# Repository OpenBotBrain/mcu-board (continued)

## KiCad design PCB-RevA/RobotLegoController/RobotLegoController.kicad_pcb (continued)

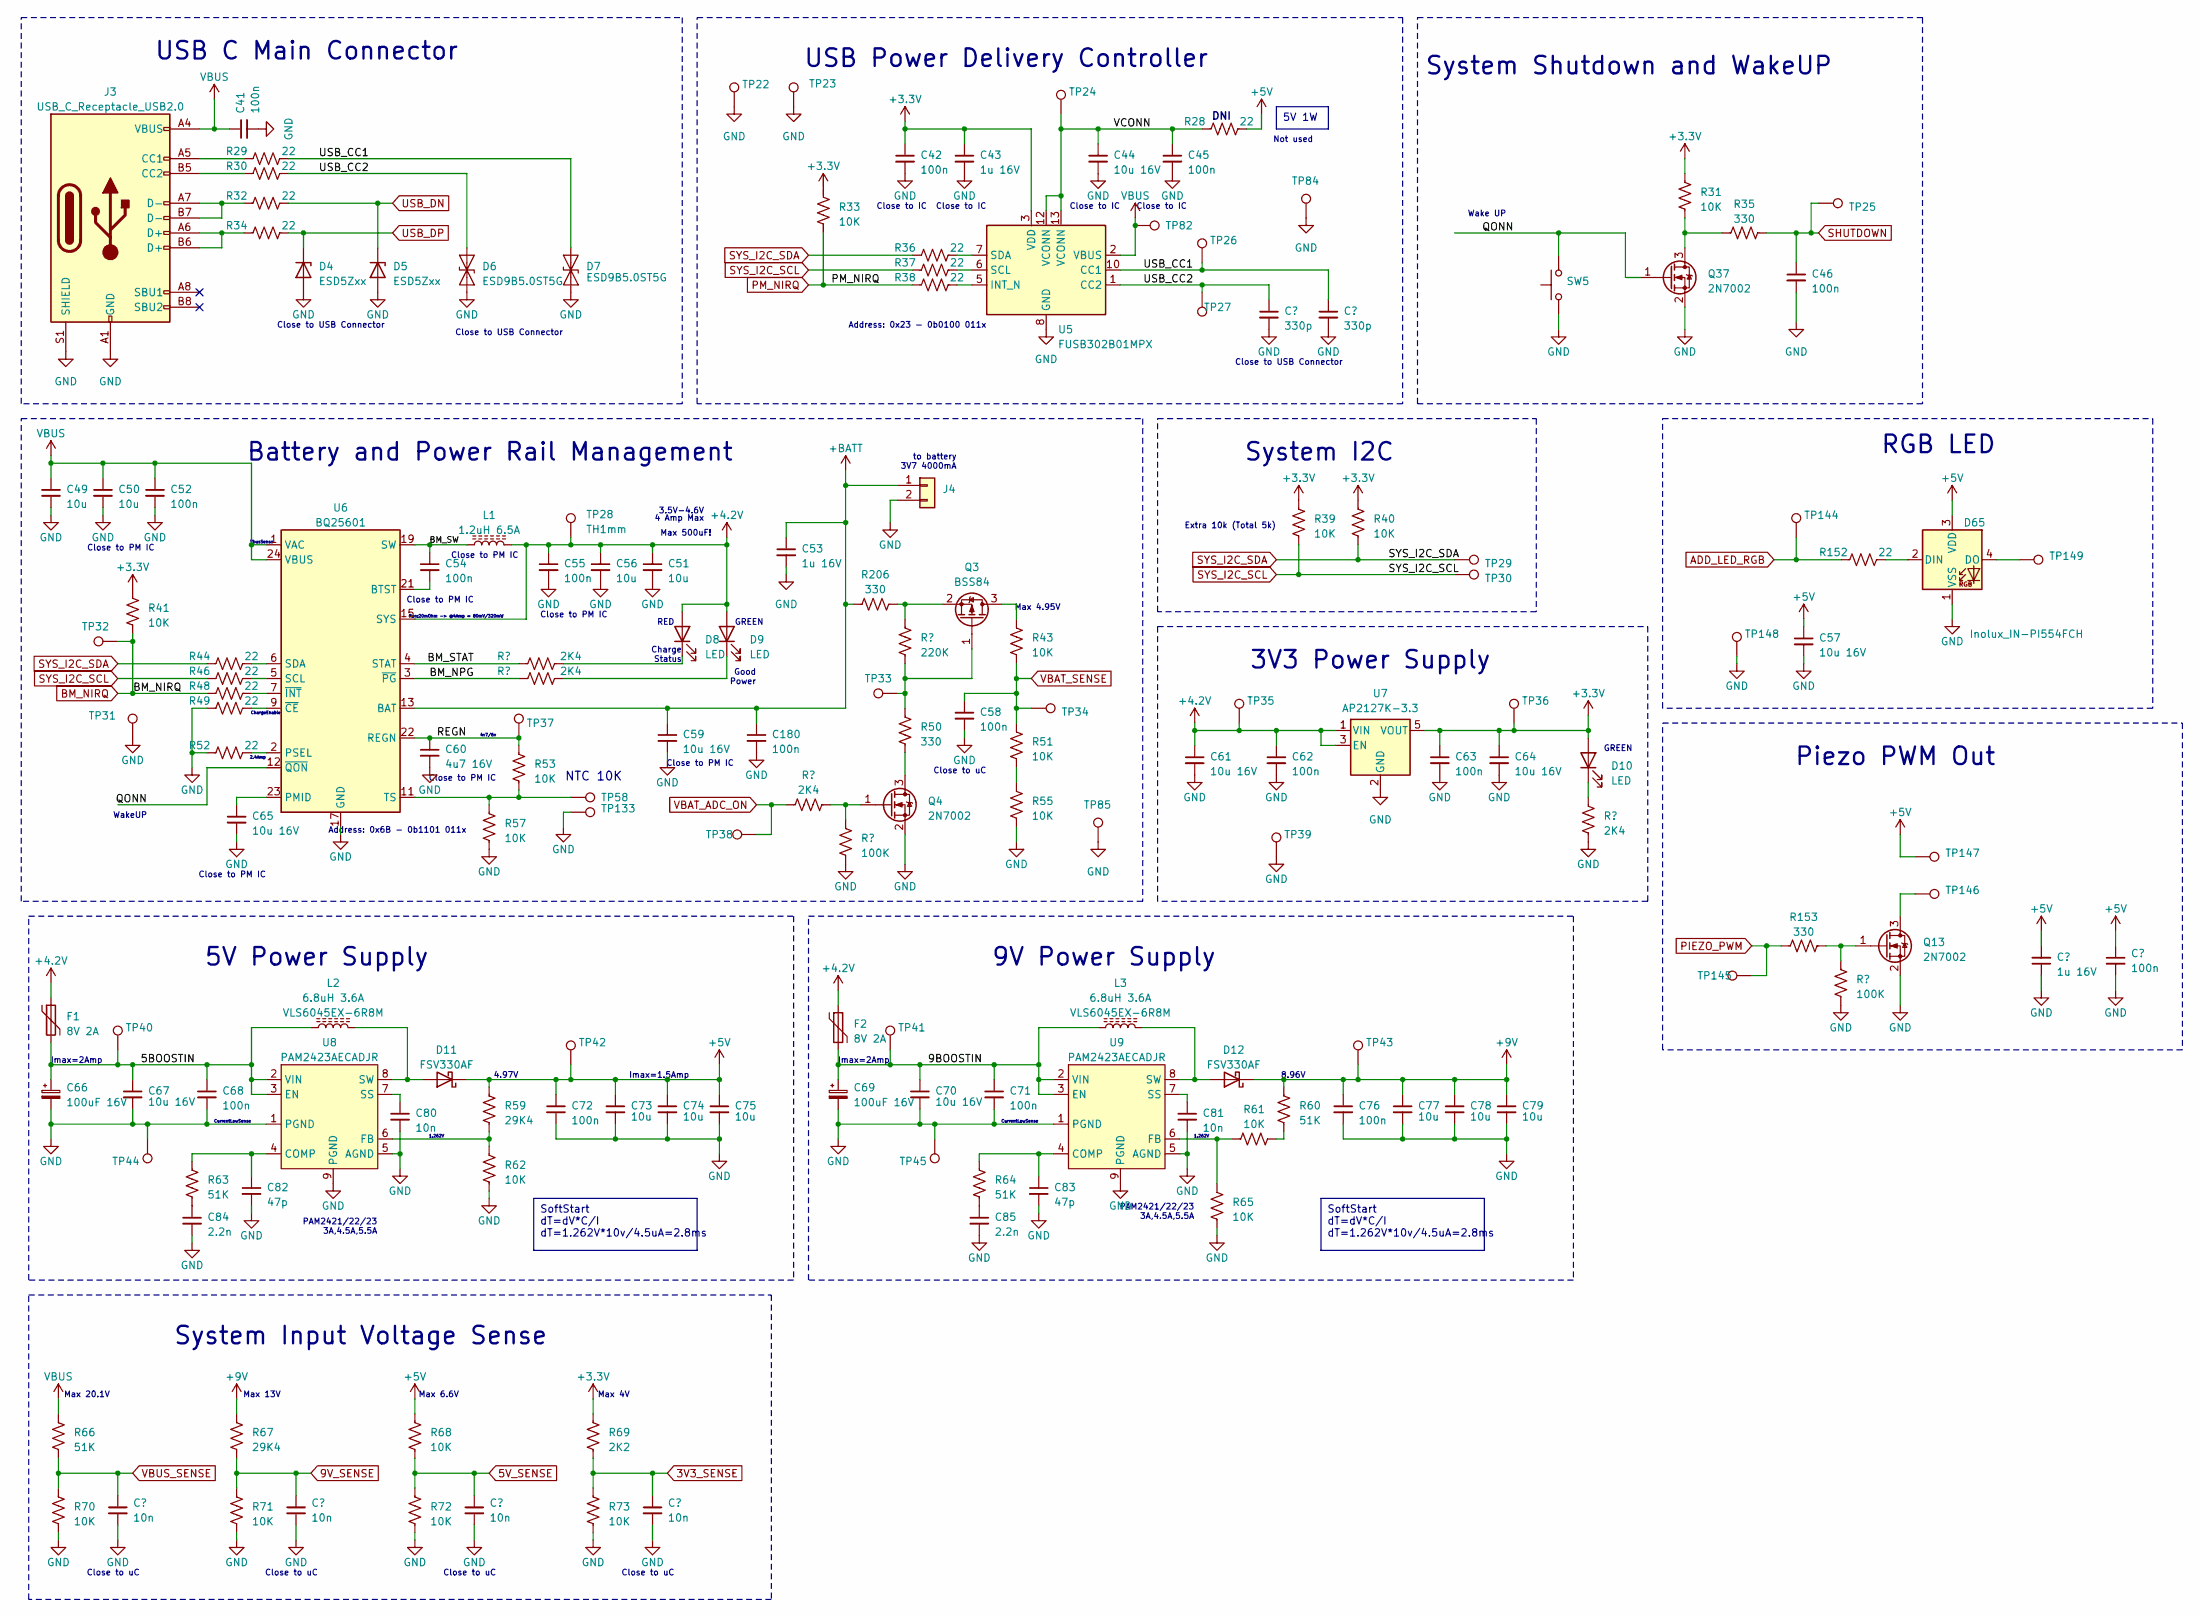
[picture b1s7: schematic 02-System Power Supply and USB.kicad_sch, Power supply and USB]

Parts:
C41, C42, C45, C46, C52, C54, C55, C58, C62, C63, C68, C71, C72, C76, C93, C180: 100n; C_0402_1005Metric
C43, C53, C92: 1u 16V; C_0603_1608Metric
C44, C57, C59, C61, C64, C65, C67, C70: 10u 16V; C_0805_2012Metric
C47, C48: 330p; C_0402_1005Metric
C49, C50, C51, C56, C73, C74, C75, C77, C78, C79: 10u; C_0805_2012Metric
C60: 4u7 16V; C_0603_1608Metric
C66, C69: 100uF 16V; CP_Elec_6.3x5.2
C80, C81, C86, C87, C88, C89: 10n; C_0402_1005Metric
C82, C83: 47p; C_0402_1005Metric
C84, C85: 2.2n; C_0402_1005Metric
D4, D5: ESD5Zxx; D_SOD-523
D6, D7: ESD9B5.0ST5G; D_SOD-923
D8, D9, D10: LED; LED_0402_1005Metric
D11, D12: FSV330AF; D_SOD-128
D65: Inolux_IN-PI554FCH; LED_Inolux_IN-PI554FCH_PLCC4_5.0x5.0mm_P3.2mm
F1, F2: 8V 2A; R_1812_4532Metric
J3: USB_C_Receptacle_USB2.0; USB_C_Receptacle_Palconn_UTC16-G
J4: Conn_01x02; JST_PH_B2B-PH-K_1x02_P2.00mm_Vertical
L1: 1.2uH 6.5A; L_Chilisin_BMRA00050520
L2, L3: 6.8uH 3.6A; L_Ferrocore_DLG-0504
Q3: BSS84; SOT-23
Q4, Q13, Q37: 2N7002; SOT-23
R28, R29, R30, R32, R34, R36, R37, R38, R44, R46, R48, R49, R52, R152: 22; R_0402_1005Metric
R31, R33, R39, R40, R41, R43, R51, R53, R55, R57, R61, R62, R65, R68, R70, R71, R72, R73: 10K; R_0402_1005Metric
R35, R50, R153, R206: 330; R_0402_1005Metric
R45, R47, R54, R56: 2K4; R_0402_1005Metric
R58, R154: 100K; R_0402_1005Metric
R59, R67: 29K4; R_0402_1005Metric
R60, R63, R64, R66: 51K; R_0402_1005Metric
R69: 2K2; R_0402_1005Metric
R168: 220K; R_0402_1005Metric
SW5: SW_Omron_B3FS; SW_Push_1P1T_NO_6x6mm_H9.5mm
TP22, TP24, TP25, TP26, TP27, TP29, TP30, TP31, TP32, TP33, TP34, TP35, TP36, TP37, TP38, TP39, TP40, TP41, TP42, TP43, TP44, TP45, TP58, TP82, TP84, TP85, TP144, TP145, TP148: S1mm; TestPoint_Pad_1.0x1.0mm
TP23, TP28, TP133, TP146, TP147, TP149: TH1mm; TestPoint_THTPad_1.0x1.0mm_Drill0.5mm
U5: FUSB302B01MPX; WQFN-14-1EP_2.5x2.5mm_P0.5mm_EP1.45x1.45mm
U6: BQ25601; Texas_S-PWQFN-N24_EP2.7x2.7mm_ThermalVias
U7: AP2127K-3.3; SOT-23-5
U8, U9: PAM2423AECADJR; SOIC-8-1EP_3.9x4.9mm_P1.27mm_EP2.29x3mm_ThermalVias

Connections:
3V3_SENSE: C89.1, R69.1, R73.2; also elsewhere on the board
5V_SENSE: C88.1, R68.1, R72.2; also elsewhere on the board
9V_SENSE: C87.1, R67.1, R71.2; also elsewhere on the board
+3.3V: C42.1, C43.1, C63.1, C64.1, D10.2 (A), R31.2, R33.2, R39.2, R40.2, R41.2, R69.2, TP36.1, U5.3 (VDD), U5.4 (VDD), U7.5 (VOUT); also elsewhere on the board
+4V: C51.1, C55.1, C56.1, C61.1, C62.1, D8.2 (A), D9.2 (A), F1.1, F2.1, L1.2, TP28.1, TP35.1, U6.15 (SYS), U6.16 (SYS), U7.1 (VIN), U7.3 (EN)
+9V: C76.1, C77.1, C78.1, C79.1, D12.1 (K), R60.2, R67.2, TP43.1; also elsewhere on the board
+BATT: C53.1, C59.1, C180.1, J4.1, R206.1, U6.13 (BAT), U6.14 (BAT)
/02-System Power Supply and USB/5BOOSTIN: C66.1, C67.1, C68.1, F1.2, L2.1, TP40.1, U8.2 (VIN), U8.3 (EN)
/02-System Power Supply and USB/9BOOSTIN: C69.1, C70.1, C71.1, F2.2, L3.1, TP41.1, U9.2 (VIN), U9.3 (EN)
/02-System Power Supply and USB/BM_NPG: R47.1, U6.3 (~PG)
/02-System Power Supply and USB/BM_STAT: R45.1, U6.4 (STAT)
/02-System Power Supply and USB/BM_SW: C54.1, L1.1, U6.19 (SW), U6.20 (SW)
/02-System Power Supply and USB/REGN: C60.1, R53.2, TP37.1, U6.22 (REGN)
/02-System Power Supply and USB/USB_CC1: C48.1, D7.2 (A2), R29.2, TP26.1, U5.10 (CC1), U5.11 (CC1)
/02-System Power Supply and USB/USB_CC2: C47.1, D6.2 (A2), R30.2, TP27.1, U5.1 (CC2), U5.14 (CC2)
/02-System Power Supply and USB/VCONN: C44.1, C45.1, R28.1, TP24.1, U5.12 (VCONN), U5.13 (VCONN)
ADD_LED_RGB: R152.1, TP144.1; also elsewhere on the board
BM_NIRQ: R41.1, R48.1, TP32.1; also elsewhere on the board
unnamed: C84.1, R63.1
unnamed: C85.1, R64.1
unnamed: D8.1 (K), R45.2
unnamed: D9.1 (K), R47.2
unnamed: D10.1 (K), R56.2
unnamed: D11.2 (A), L2.2, U8.8 (SW)
unnamed: D12.2 (A), L3.2, U9.8 (SW)
unnamed: D65.2 (DIN), R152.2
unnamed: D65.4 (DO), TP149.1
unnamed: J3.A5 (CC1), R29.1
unnamed: J3.B5 (CC2), R30.1
unnamed: J3.A6 (D+), J3.B6 (D+), R34.1
unnamed: J3.A7 (D-), J3.B7 (D-), R32.1
unnamed: Q3.3 (D), R43.2
unnamed: Q4.3 (D), R50.2
unnamed: Q4.1 (G), R54.2, R58.2
unnamed: Q13.3 (D), TP146.1
unnamed: Q13.1 (G), R153.1, R154.2
unnamed: Q37.3 (D), R31.1, R35.2
unnamed: R51.1, R55.2
unnamed: R60.1, R61.1
unnamed: R38.2, U5.5 (INT_N)
unnamed: R37.2, U5.6 (SCL)
unnamed: R36.2, U5.7 (SDA)
unnamed: C54.2, U6.21 (BTST)
unnamed: C65.1, U6.23 (PMID)
unnamed: R52.2, U6.2 (PSEL)
unnamed: R46.2, U6.5 (SCL)
unnamed: R44.2, U6.6 (SDA)
unnamed: R53.1, R57.2, TP58.1, U6.11 (TS)
unnamed: R49.2, U6.9 (~CE)
unnamed: R48.2, U6.7 (~INT)
unnamed: C82.1, R63.2, U8.4 (COMP)
unnamed: R59.1, R62.2, U8.6 (FB)
unnamed: C80.1, U8.7 (SS)
unnamed: C83.1, R64.2, U9.4 (COMP)
unnamed: R61.2, R65.2, U9.6 (FB)
unnamed: C81.1, U9.7 (SS)
PIEZO_PWM: R153.2, TP145.1; also elsewhere on the board
PM_NIRQ: R33.1, R38.1; also elsewhere on the board
SHUTDOWN: C46.1, R35.1, TP25.1; also elsewhere on the board
SYS_I2C_SCL: R37.1, R39.1, R46.1, TP30.1; also elsewhere on the board
SYS_I2C_SDA: R36.1, R40.1, R44.1, TP29.1; also elsewhere on the board
USB_DN: D5.1 (K), R32.2; also elsewhere on the board
USB_DP: D4.1 (K), R34.2; also elsewhere on the board
VBAT_ADC_ON: R54.1, TP38.1; also elsewhere on the board
VBAT_SENSE: C58.1, R43.1, R51.2, TP34.1; also elsewhere on the board
VBUS_SENSE: C86.1, R66.1, R70.2; also elsewhere on the board

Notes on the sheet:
5V 1W
SoftStart dT=dV*C/I dT=1.262V*10v/4.5uA=2.8ms
3.5V-4.6V
System I2C
Close to PM IC
Imax=2Amp
Charge Status
Imax=1.5Amp
RGB LED
4.97V
Ron:20mOhm -> @4Amp = 80mV/320mW
Close to uC
USB Power Delivery Controller
Close to USB Connector
PAM2421/22/23 3A,4.5A,5.5A
Max 20.1V
Close to IC
Max 6.6V
ChargeEnable
Not used
Max 4.95V
VbusSense
9V Power Supply
WakeUP
Address: 0x6B - 0b1101 011x
2.4Amp
to battery 3V7 4000mA
System Input Voltage Sense
1.262V
5V Power Supply
4 Amp Max
USB C Main Connector
Max 13V
4v7/6v
System Shutdown and WakeUP
DNI
Address: 0x23 - 0b0100 011x
CurrentLowSense
NTC 10K
Piezo PWM Out

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
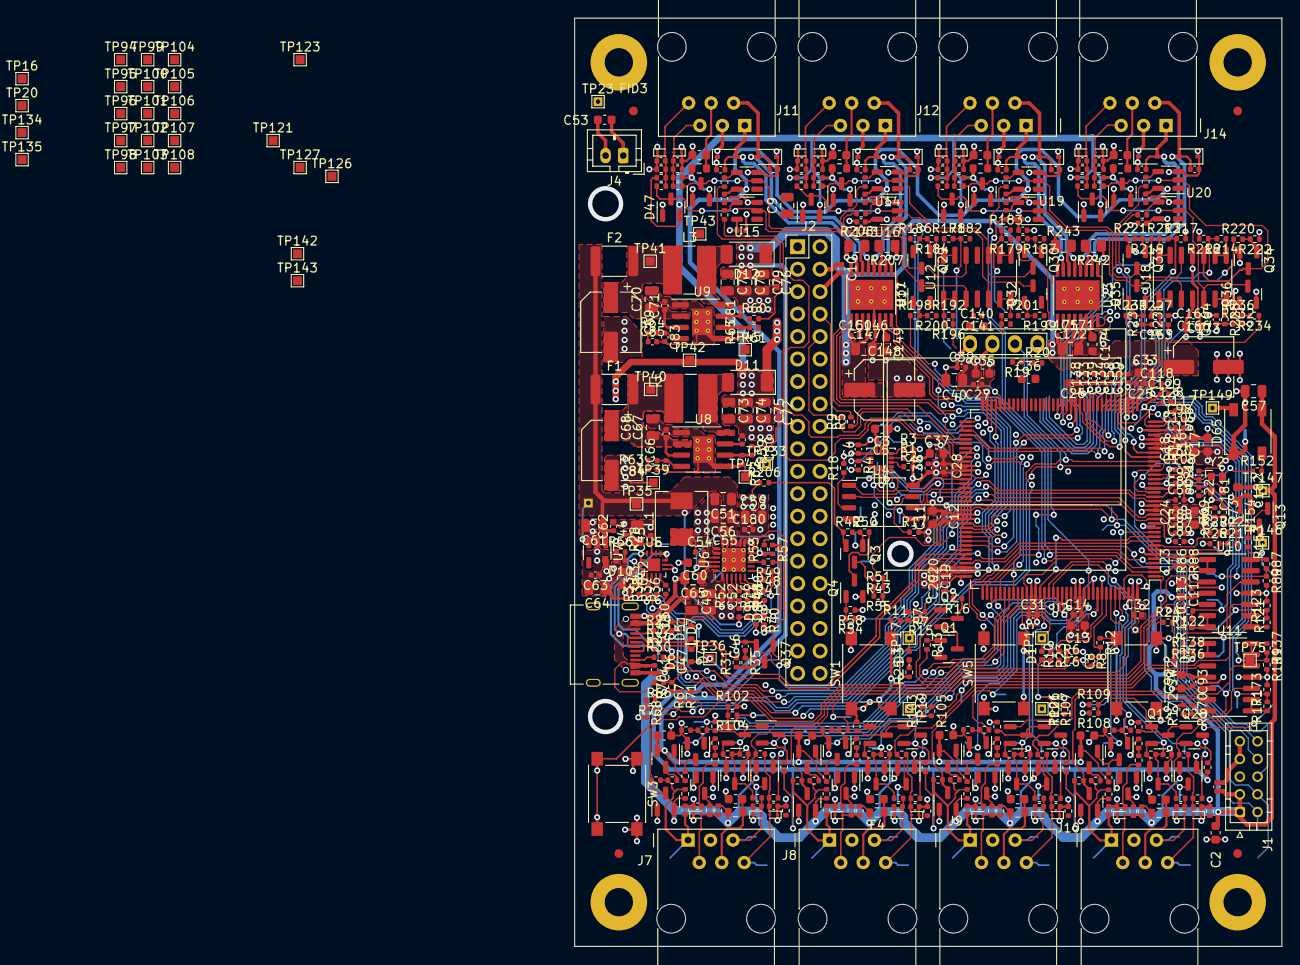
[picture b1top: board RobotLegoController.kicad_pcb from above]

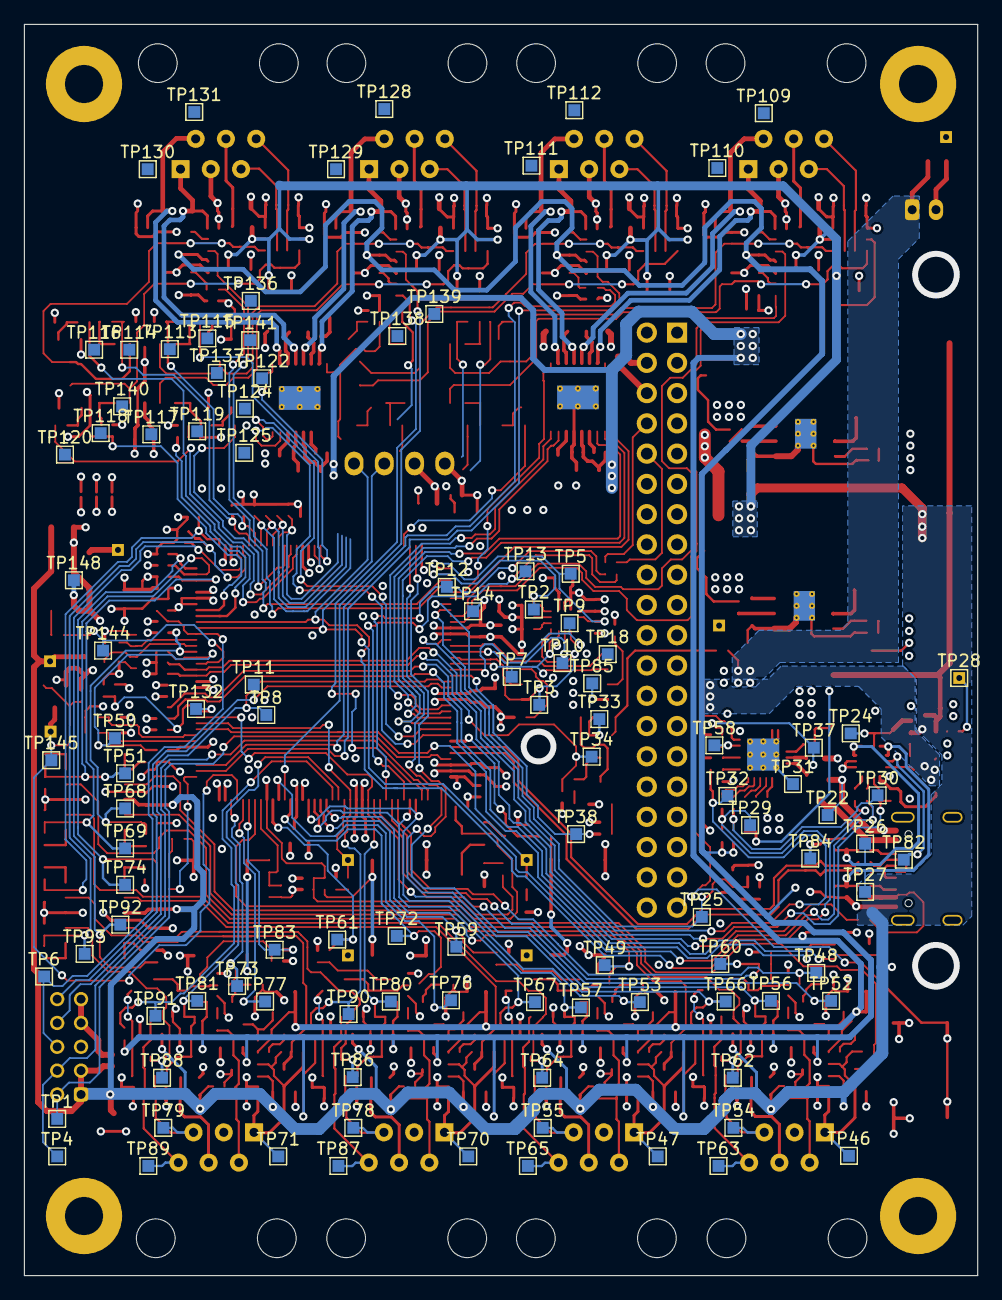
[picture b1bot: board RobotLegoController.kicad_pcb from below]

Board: 4 copper layers, 80.0 x 105.0 mm, 724 parts (105 on the bottom side), 301 nets.

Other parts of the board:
C9: 10u; C_0805_2012Metric
C133, C134, C138, C139, C158, C159, C163, C164: 10n; C_0402_1005Metric
C181: 1u 16V; C_0603_1608Metric
C182: 100n; C_0402_1005Metric
R42: 220K; R_0402_1005Metric
SW3: SW_Omron_B3FS; SW_Push_1P1T_NO_6x6mm_H9.5mm
TP136, TP137, TP138, TP139, TP140, TP141: S1mm; TestPoint_Pad_1.0x1.0mm

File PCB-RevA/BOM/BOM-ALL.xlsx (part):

Reference | Value | Footprint | Datasheet | Digi | Digikey | Field4 | Field5 | digi | Qty
C1, C4-C8, C10, C12, C14, C18, C20, C23-C32, C38, C39, C41, C42, C45, C46, C52,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 | 100n | Capacitor_SMD:C_0402_1005Metric | https://www.digikey.co.uk/en/products/detail/samsung-electro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 |  |  |  |  | https://www.digikey.co.uk/en/products/detail/samsung-electro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 | 53 |  | https://www.lcsc.com/product-detail/Multilayer-Ceramic-Capac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
C2, C3, C16, C17, C19, C33-C37, C43, C53, C90-C92, C94, C99, C110-C112, C114, C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 | 1u 16V | Capacitor_SMD:C_0603_1608Metric | https://www.digikey.co.uk/en/products/detail/samsung-electro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 |  |  |  |  | https://www.digikey.co.uk/en/products/detail/samsung-electro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 | 29 |  | https://www.lcsc.com/product-detail/Multilayer-Ceramic-Capac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
C9, C49-C51, C56, C73-C75, C77-C79 | 10u | Capacitor_SMD:C_0805_2012Metric | https://www.digikey.co.uk/en/products/detail/samsung-electro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 | https://www.digikey.co.uk/en/products/detail/samsung-electro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 |  |  |  |  | 11 |  | https://www.lcsc.com/product-detail/Multilayer-Ceramic-Capac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
C11, C13, C60, C149, C174 | 4u7 16V | Capacitor_SMD:C_0603_1608Metric | https://www.digikey.co.uk/en/products/detail/samsung-electro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 |  |  |  |  | https://www.digikey.co.uk/en/products/detail/samsung-electro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 | 5 |  | https://www.lcsc.com/product-detail/Multilayer-Ceramic-Capac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
C15, C80, C81, C86-C89, C97, C98, C108, C109, C117, C118, C128, C129, C133, C13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 | 10n | Capacitor_SMD:C_0402_1005Metric |  |  |  |  |  |  | 25 |  | https://www.lcsc.com/product-detail/Multilayer-Ceramic-Capac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
C21, C22 | 6p8 | Capacitor_SMD:C_0402_1005Metric |  |  |  |  |  |  | 2 |  | https://www.lcsc.com/product-detail/Multilayer-Ceramic-Capac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
C40, C44, C57, C59, C61, C64, C65, C67, C70, C147, C172 | 10u 16V | Capacitor_SMD:C_0805_2012Metric | https://www.digikey.co.uk/en/products/detail/samsung-electro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 | https://www.digikey.co.uk/en/products/detail/samsung-electro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 |  |  |  |  | 11 |  | https://www.lcsc.com/product-detail/Multilayer-Ceramic-Capac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
C47, C48, C95, C96, C100-C107, C115, C116, C120-C127, C130, C131, C136, C137, C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 | 330p | Capacitor_SMD:C_0402_1005Metric |  |  |  |  |  |  | 38 |  | https://www.lcsc.com/product-detail/Multilayer-Ceramic-Capac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
C66, C69, C148, C173 | 100uF 16V | Capacitor_SMD:CP_Elec_6.3x5.2 | ~ |  |  |  |  |  | 4 |  | https://www.lcsc.com/product-detail/Aluminum-Electrolytic-Ca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
C82, C83 | 47p | Capacitor_SMD:C_0402_1005Metric |  |  |  |  |  |  | 2 |  | https://www.lcsc.com/product-detail/Multilayer-Ceramic-Capac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
C84, C85 | 2.2n | Capacitor_SMD:C_0402_1005Metric |  |  |  |  |  |  | 2 |  | https://www.lcsc.com/product-detail/Multilayer-Ceramic-Capac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
D1-D3, D8-D10 | LED | LED_SMD:LED_0402_1005Metric | ~ |  |  |  |  |  | 6 |  | https://www.lcsc.com/product-detail/Light-Emitting-Diodes-LE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
D4, D5 | ESD5Zxx | Diode_SMD:D_SOD-523 | https://www.onsemi.com/pdf/datasheet/esd5z2.5t1-d.pdf |  |  | https://www.digikey.co.uk/en/products/detail/littelfuse-inc/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 |  |  | 2 |  | https://www.lcsc.com/product-detail/span-style-background-co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
D6, D7, D17, D18, D21, D22, D25, D26, D31, D32, D35, D36, D39-D42, D45, D46, D5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 | ESD9B5.0ST5G | Diode_SMD:D_SOD-923 | https://www.onsemi.com/pub/Collateral/ESD9B-D.PDF |  |  |  |  |  | 22 |  | https://www.lcsc.com/product-detail/span-style-background-co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
D11, D12 | FSV330AF | Diode_SMD:D_SOD-128 | ~ |  |  |  |  |  | 2 |  | https://www.lcsc.com/product-detail/Schottky-Barrier-Diodes-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
D13-D16, D19, D20, D23, D24, D27-D30, D33, D34, D37, D38, D43, D44, D47, D48, D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 | BAT54S | Package_TO_SOT_SMD:SOT-23 | https://www.diodes.com/assets/Datasheets/ds11005.pdf |  |  |  |  |  | 24 |  | https://www.lcsc.com/product-detail/Schottky-Barrier-Diodes-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
D49-D52, D61-D64 | SD12_SOD323 | Diode_SMD:D_SOD-323 | https://www.littelfuse.com/~/media/electronics/datasheets/tv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 |  |  |  |  |  | 8
D65 | Inolux_IN-PI554FCH | LED_SMD:LED_Inolux_IN-PI554FCH_PLCC4_5.0x5.0mm_P3.2mm | http://www.inolux-corp.com/datasheet/SMDLED/Addressable%20LE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 |  |  |  |  |  | 1 |  | https://www.lcsc.com/product-detail/Light-Emitting-Diodes-LE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
F1, F2 | 8V 2A | Resistor_SMD:R_1812_4532Metric | https://www.digikey.co.uk/en/products/detail/bel-fuse-inc/0Z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 |  |  |  |  |  | 2 |  | https://www.lcsc.com/product-detail/Resettable-Fuses_BHFUSE-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
F3-F10 | 30mA | Resistor_SMD:R_0603_1608Metric | https://www.digikey.co.uk/en/products/detail/bel-fuse-inc/0Z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 |  |  |  |  |  | 8 |  | https://www.lcsc.com/product-detail/Resettable-Fuses_BHFUSE-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
FID1-FID4 | Fiducial | Fiducial:Fiducial_1mm_Mask3mm | ~ |  |  |  |  |  | 4
H1-H4 | 3mm | MountingHole:MountingHole_3.2mm_M3_Pad | ~ |  |  |  |  |  | 4
J1 | DF11-10DP-2DSA | Connector_JST:JST_PHD_B10B-PHDSS_2x05_P2.00mm_Vertical | ~ |  |  |  |  |  | 1 |  | https://www.lcsc.com/product-detail/Wire-To-Board-Wire-To-Wi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
J2 | Raspberry_Pi_2_3 | Connector_PinHeader_2.54mm:PinHeader_2x20_P2.54mm_Vertical | https://www.raspberrypi.org/documentation/hardware/raspberry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 |  |  |  |  |  | 1
J3 | USB_C_Receptacle_USB2.0 | Connector_USB:USB_C_Receptacle_Palconn_UTC16-G | https://www.usb.org/sites/default/files/documents/usb_type-c.zip |  |  |  |  |  | 1 |  | https://www.lcsc.com/product-detail/USB-Connectors_G-Switch-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
J4 | Conn_01x02 | Connector_JST:JST_PH_B2B-PH-K_1x02_P2.00mm_Vertical | https://www.digikey.co.uk/en/products/detail/jst-sales-ameri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 |  |  |  |  |  | 1
J7-J14 | RJ12 | Connector_RJ:RJ12_Amphenol_54601 | https://www.digikey.co.uk/en/products/detail/assmann-wsw-com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 |  |  |  |  |  | 8 |  | n/a
L1 | 1.2uH 6.5A | Inductor_SMD:L_Chilisin_BMRA00050520 | https://www.digikey.co.uk/en/products/detail/susumu/PCMB053T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 |  |  |  |  |  | 1 |  | n/a
L2, L3 | 6.8uH 3.6A | Inductor_SMD:L_Ferrocore_DLG-0504 | https://www.digikey.co.uk/en/products/detail/tdk-corporation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 |  |  | VLS6045EX-6R8M |  |  | 2 |  | https://www.lcsc.com/product-detail/Inductors-SMD_KOHERelec-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
Q1-Q3, Q5, Q6, Q9-Q12, Q17, Q18 | BSS84 | Package_TO_SOT_SMD:SOT-23 | http://assets.nexperia.com/documents/data-sheet/BSS84.pdf |  |  |  |  |  | 11 |  | https://www.lcsc.com/product-detail/MOSFETs_FOSAN-BSS84_C292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
Q4, Q7, Q8, Q13, Q15, Q16, Q19, Q20, Q27-Q37 | 2N7002 | Package_TO_SOT_SMD:SOT-23 | https://www.onsemi.com/pub/Collateral/NDS7002A-D.PDF |  |  |  |  |  | 19 |  | https://www.lcsc.com/product-detail/MOSFETs_JSMSEMI-2N7002_C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
R1-R4, R6-R8, R13-R20, R31, R33, R39-R41, R43, R51, R53, R55, R57, R61, R62, R6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 | 10K | Resistor_SMD:R_0402_1005Metric | ~ |  |  |  |  |  | 65 |  | https://www.lcsc.com/product-detail/Chip-Resistor-Surface-Mo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
R5, R9, R28-R30, R32, R34, R36-R38, R44, R46, R48, R49, R52, R152 | 22 | Resistor_SMD:R_0402_1005Metric | ~ |  |  |  |  |  | 16 |  | https://www.lcsc.com/product-detail/Chip-Resistor-Surface-Mo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
R10-R12, R23-R25, R35, R50, R78-R81, R100, R101, R104, R105, R107, R109, R113, 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 | 330 | Resistor_SMD:R_0402_1005Metric | ~ |  |  |  |  |  | 46 |  | https://www.lcsc.com/product-detail/Chip-Resistor-Surface-Mo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
R21, R22, R26, R27, R45, R47, R54, R56, R69, R86, R87, R120, R121, R136, R137, 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 | 2K4 | Resistor_SMD:R_0402_1005Metric | ~ |  |  |  |  |  | 25 |  | https://www.lcsc.com/product-detail/Chip-Resistor-Surface-Mo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
R42, R116, R118, R166, R168 | 220K | Resistor_SMD:R_0402_1005Metric | ~ |  |  |  |  |  | 5 |  | https://www.lcsc.com/product-detail/Chip-Resistor-Surface-Mo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
R58, R76, R77, R82, R83, R98, R99, R102, R103, R106, R108, R117, R119, R126, R1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 | 100K | Resistor_SMD:R_0402_1005Metric | ~ |  |  |  |  |  | 46 |  | https://www.lcsc.com/product-detail/Chip-Resistor-Surface-Mo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
R59, R67 | 29K4 | Resistor_SMD:R_0402_1005Metric | ~ | https://www.digikey.co.uk/en/products/detail/stackpole-elect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 |  |  |  |  | 2 |  | https://www.lcsc.com/product-detail/Chip-Resistor-Surface-Mo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
R60, R63, R64, R66 | 51K | Resistor_SMD:R_0402_1005Metric | ~ | https://www.digikey.co.uk/en/products/detail/stackpole-elect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 |  |  |  |  | 4 |  | https://www.lcsc.com/product-detail/Chip-Resistor-Surface-Mo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

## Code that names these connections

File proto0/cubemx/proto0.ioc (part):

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Mcu.Name=STM32L4Q5CGTx
Mcu.Package=LQFP48
Mcu.UserName=STM32L4Q5CGTx
PA0.Mode=CTS_Only
PA0.Signal=USART2_CTS
PA1.Mode=SD_1_bit
PA1.Signal=SDMMC2_CMD
PA10.Mode=Asynchronous
PA10.Signal=USART1_RX
PA11.Mode=CAN_Activate
PA11.Signal=CAN1_RX
PA12.Mode=CAN_Activate
PA12.Signal=CAN1_TX
PA2.Mode=Asynchronous
PA2.Signal=USART2_TX
PA3.Mode=Asynchronous
PA3.Signal=USART2_RX
PA4.Mode=NSS_Signal_Hard_Input
PA4.Signal=SPI1_NSS
PA5.Mode=Full_Duplex_Master
PA5.Signal=SPI1_SCK
PA6.Mode=Full_Duplex_Master
PA6.Signal=SPI1_MISO
PA7.Mode=I2C
PA7.Signal=I2C3_SCL
PA9.Mode=Asynchronous
PA9.Signal=USART1_TX
PB10.Mode=Simplex_Bidirectional_Master
PB10.Signal=SPI2_SCK
PB11.Mode=I2C
PB11.Signal=I2C2_SDA
PB12.Mode=SD_1_bit
PB12.Signal=SDMMC2_CK
PB13.Mode=I2C
PB13.Signal=I2C2_SCL
PB14.Mode=SD_1_bit
PB14.Signal=SDMMC2_D0
PB15.Mode=Simplex_Bidirectional_Master
PB15.Signal=SPI2_MOSI
PB4\ (NJTRST).Mode=I2C
PB4\ (NJTRST).Signal=I2C3_SDA
PB5.Mode=Full_Duplex_Master
PB5.Signal=SPI1_MOSI
PB6.Mode=I2C
PB6.Signal=I2C4_SCL
PB7.Mode=I2C
PB7.Signal=I2C4_SDA
PB8.Mode=I2C
PB8.Signal=I2C1_SCL
PB9.Mode=I2C
PB9.Signal=I2C1_SDA
RCC.HSE_VALUE=8000000
board=custom

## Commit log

2022-10-23 update the readme with some design ideas
2022-10-23 cosmetic changes
2022-10-23 mention ESP32 S3 too
2022-10-23 added some options for MCU
2022-10-23 application note link
2022-10-23 new MCU option
2022-10-23 typo
2022-10-24 added a new smaller STM32 option
2022-10-24 added gitignore
2022-11-02 add the cubeMX and the kicad file
2022-11-21 add power supply to MCU
2022-11-21 add reset button and anti-bouncing capacitor
2022-11-21 add boot switch
2022-11-21 improve layout
2022-12-05 added more sheets and started doing the ports
2022-12-05 update gitignore
2023-02-25 Add initial kicad pcb file
2023-02-25 Change motor and inputs to A~D names instead of number, fix dipswich
2023-02-25 Extra pcb routing
2023-02-25 More routing done on the pcb
2023-02-26 Finish routing inputs
2023-02-27 New pcb update on motor frontend
2023-02-28 More pcb routing done
2023-03-01 More advance on pcb
2023-03-03 More and more pcb routing. Most input frontend done
2023-03-04 More and more pcb routing
2023-03-04 yeap, more time routing the PCB
2023-03-06 Working on motor routing, now motor c and d are done
2023-03-06 Add some 3v3 routing into the pcb
2023-03-07 Finishing connecting most of the nets
2023-03-07 Start working on pcn details
2023-03-07 Mosly done with silkscreen
2023-03-07 Mosly done with crcs
2023-03-08 PCB is finally done
2023-03-09 Done with schematic and pcb
2023-03-14 Update board name
2023-03-16 Add bom and intial p and p files
2023-03-20 Update pcb, bom and p and p files
2023-03-20 Rework bom
2023-03-20 Finish PAP and BOM
